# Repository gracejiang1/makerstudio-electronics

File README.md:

# makerstudio-electronics
Training board designs

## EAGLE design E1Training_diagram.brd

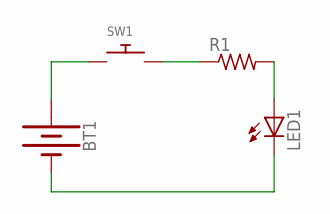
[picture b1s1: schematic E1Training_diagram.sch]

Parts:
BT1: BATTERY-20MM_PTH; BATTCOM_20MM_PTH
LED1: LED5MM
R1: R-US_0204/7; 0204/7
SW1: SWITCH_PUSHBUTTONEVQ-PE; TACT_PANA-EVQ

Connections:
unnamed: BT1.1 (+), SW1.P$1
unnamed: R1.1, SW1.P$2
unnamed: LED1.A, R1.2
unnamed: BT1.2 (-), LED1.K (C)

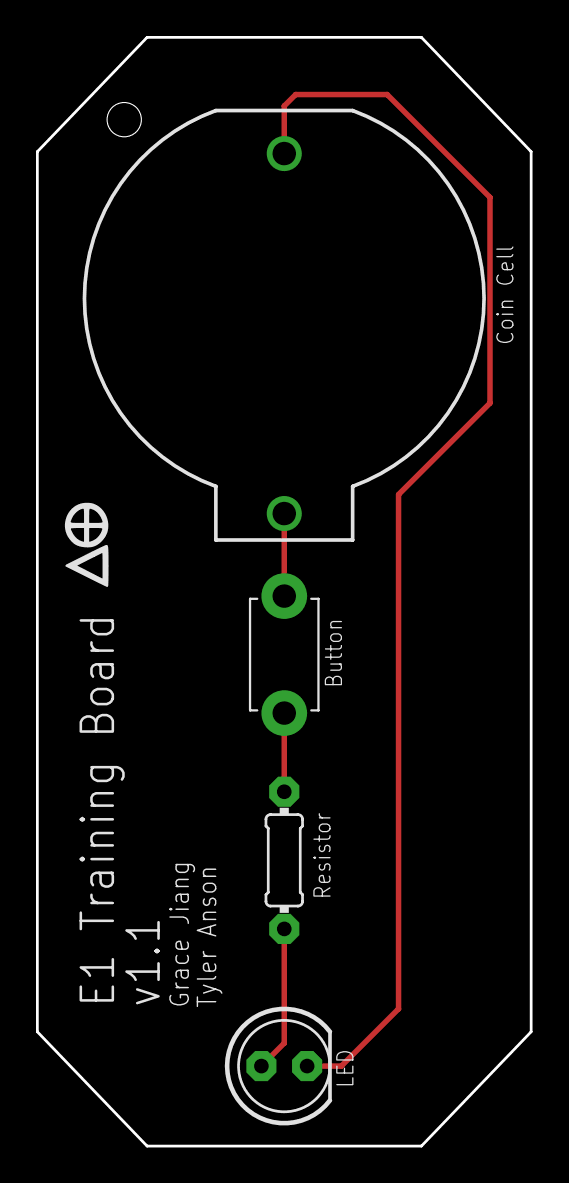
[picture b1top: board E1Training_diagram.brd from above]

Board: 2 copper layers, 27.4 x 61.6 mm, 4 parts (0 on the bottom side), 4 nets.

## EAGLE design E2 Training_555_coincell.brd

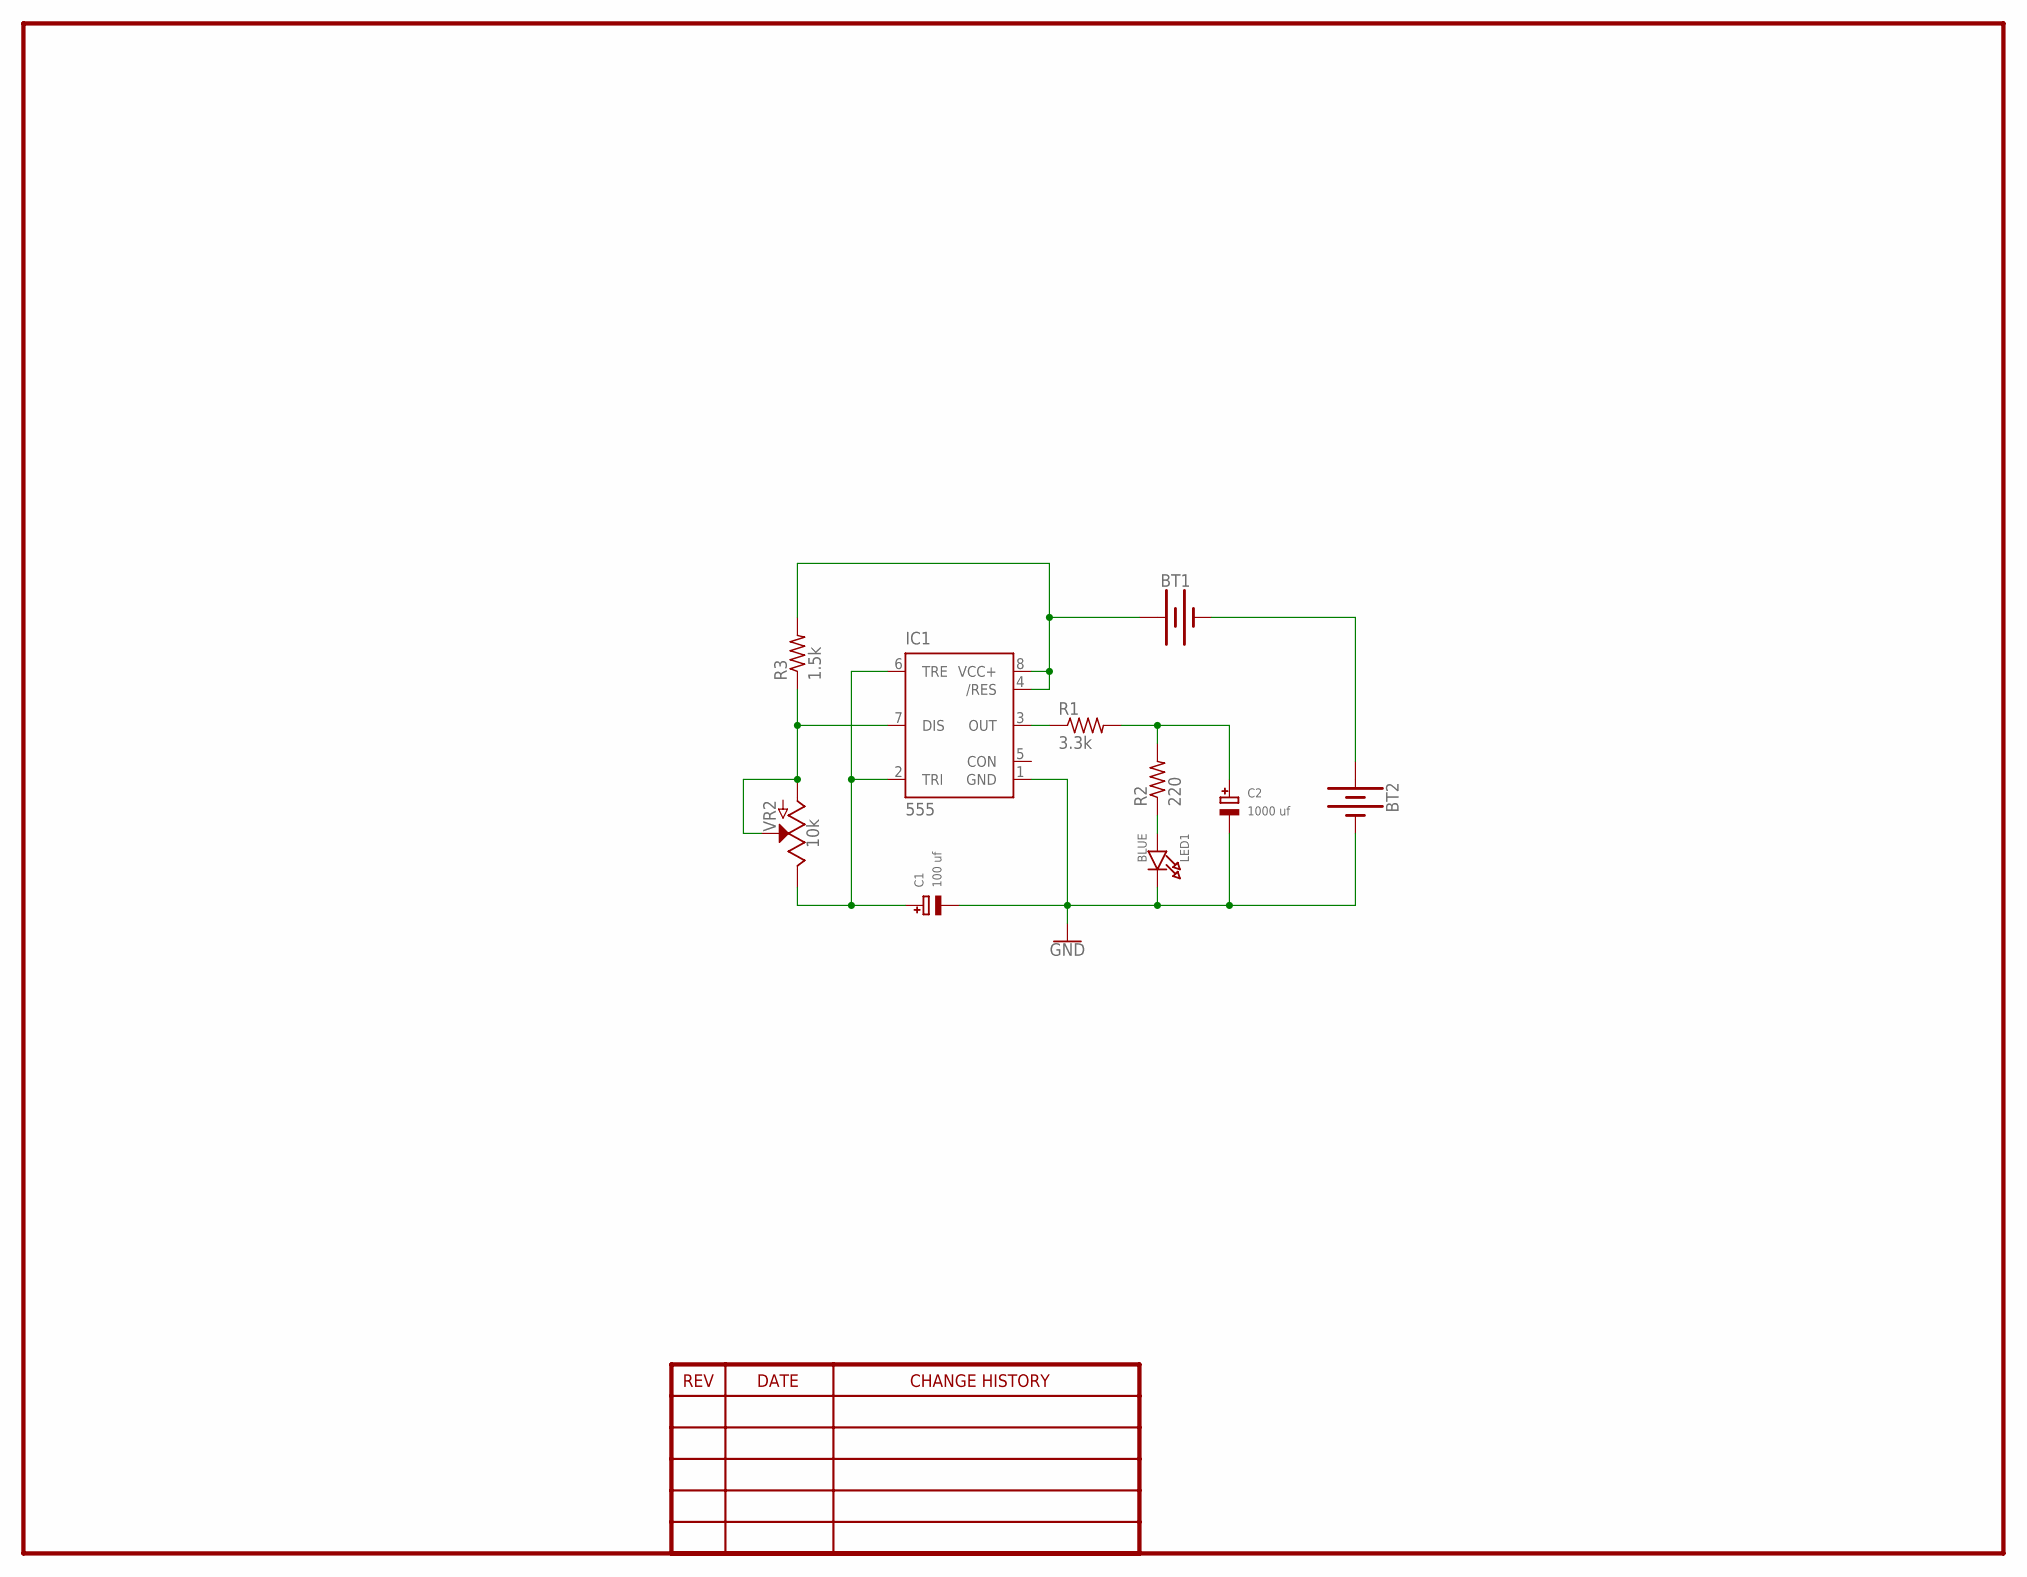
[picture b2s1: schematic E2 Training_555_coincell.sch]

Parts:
BT1, BT2: BATTERY-20MM_PTH; BATTCOM_20MM_PTH
C1: 100 uf; EIA7343-31/D-R
C2: 1000 uf; EIA7343-31/D-R
IC1: 555; SO08
LED1: BLUE; CHIPLED_0805
R1: 3.3k; M0805
R2: 220; M0805
R3: 1.5k; M0805
VR2: 10k; POT-PTH-ALPS

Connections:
GND: BT2.2 (-), C1.-, C2.-, IC1.1 (GND), LED1.C
unnamed: IC1.3 (OUT), R1.1
unnamed: C2.+, R1.2, R2.2
unnamed: LED1.A, R2.1
unnamed: C1.+, IC1.2 (TRI), IC1.6 (TRE), VR2.P$1 (E)
unnamed: IC1.7 (DIS), R3.1, VR2.P$2 (S), VR2.P$3 (A)
unnamed: BT1.2 (-), BT2.1 (+)
VCC: BT1.1 (+), IC1.4 (/RES), IC1.8 (VCC+), R3.2

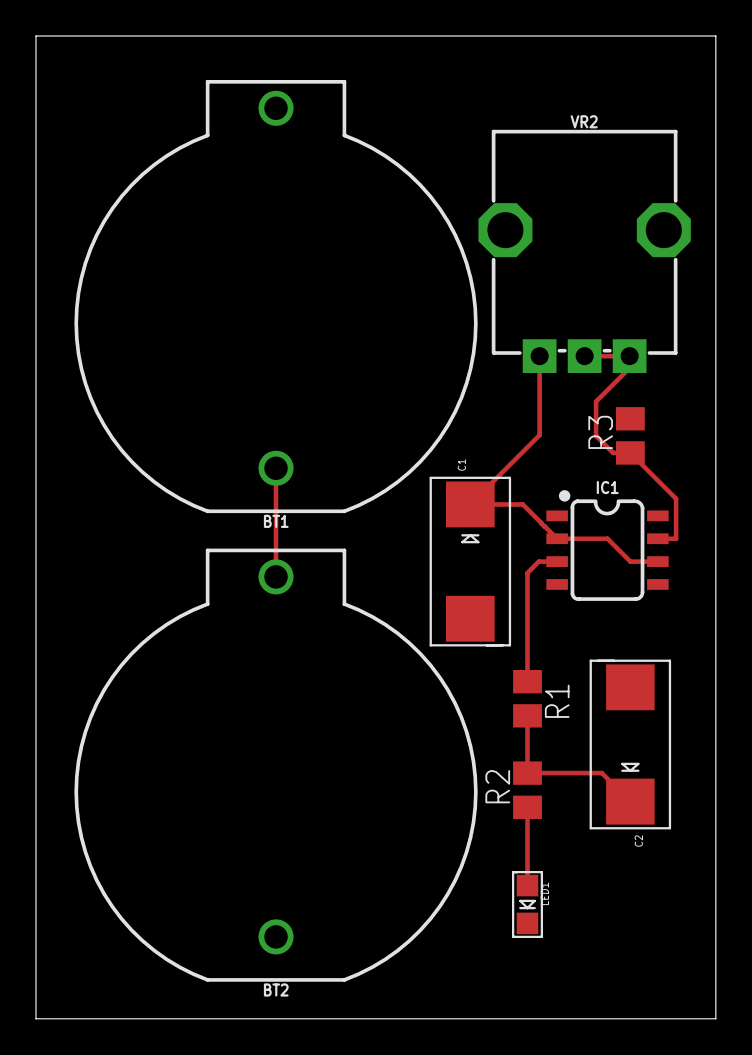
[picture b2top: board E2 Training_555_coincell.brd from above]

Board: 2 copper layers, 37.8 x 54.6 mm, 10 parts (0 on the bottom side), 8 nets.

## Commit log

2019-10-23 E2_Training_555_coincell
    added first draft of 555 SMD training board
2019-10-23 added E1 training board and schematic on back

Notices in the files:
parts and their libraries:
SparkFun-Batteries: Licensing: Creative Commons ShareAlike 4.0 International - https://creativecommons.org/licenses/by-sa/4.0
dframes: Copyright (C) 2004, Bob Starr (bobstarr@mindspring.com)
